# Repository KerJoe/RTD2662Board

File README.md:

# RTD2662Board

Prototype board for developing RTD2662 firmware.

## Known problems
1. CH341 can work either in I2C or UART mode, but not both at once. If R87 is present I2C mode is enabled, otherwise the UART is used. 
The "Mods/bridgeReplacementBoard" folder contains a patch PCB using MCP2221. While it is possible to use both I2C and UART parts simultaneously, I have experienced connection problems with it's USB interface.
2. The 3.3 volt rail lacks filtering enough capacitance, so it may be necessary to add an extra 100uF electrolytic capacitor across it and ground. The C78 capacitor was added to rectify the problem, but was not tested.
3. While TPS61040 can be used for driving an LED backlight, it requires a Zener diode between "BLO_ANO" line and ground, otherwise if the screen is disconnected it will output too much voltage and self destruct. A PT4103 or similar is recommended for the U5 backlight driver.

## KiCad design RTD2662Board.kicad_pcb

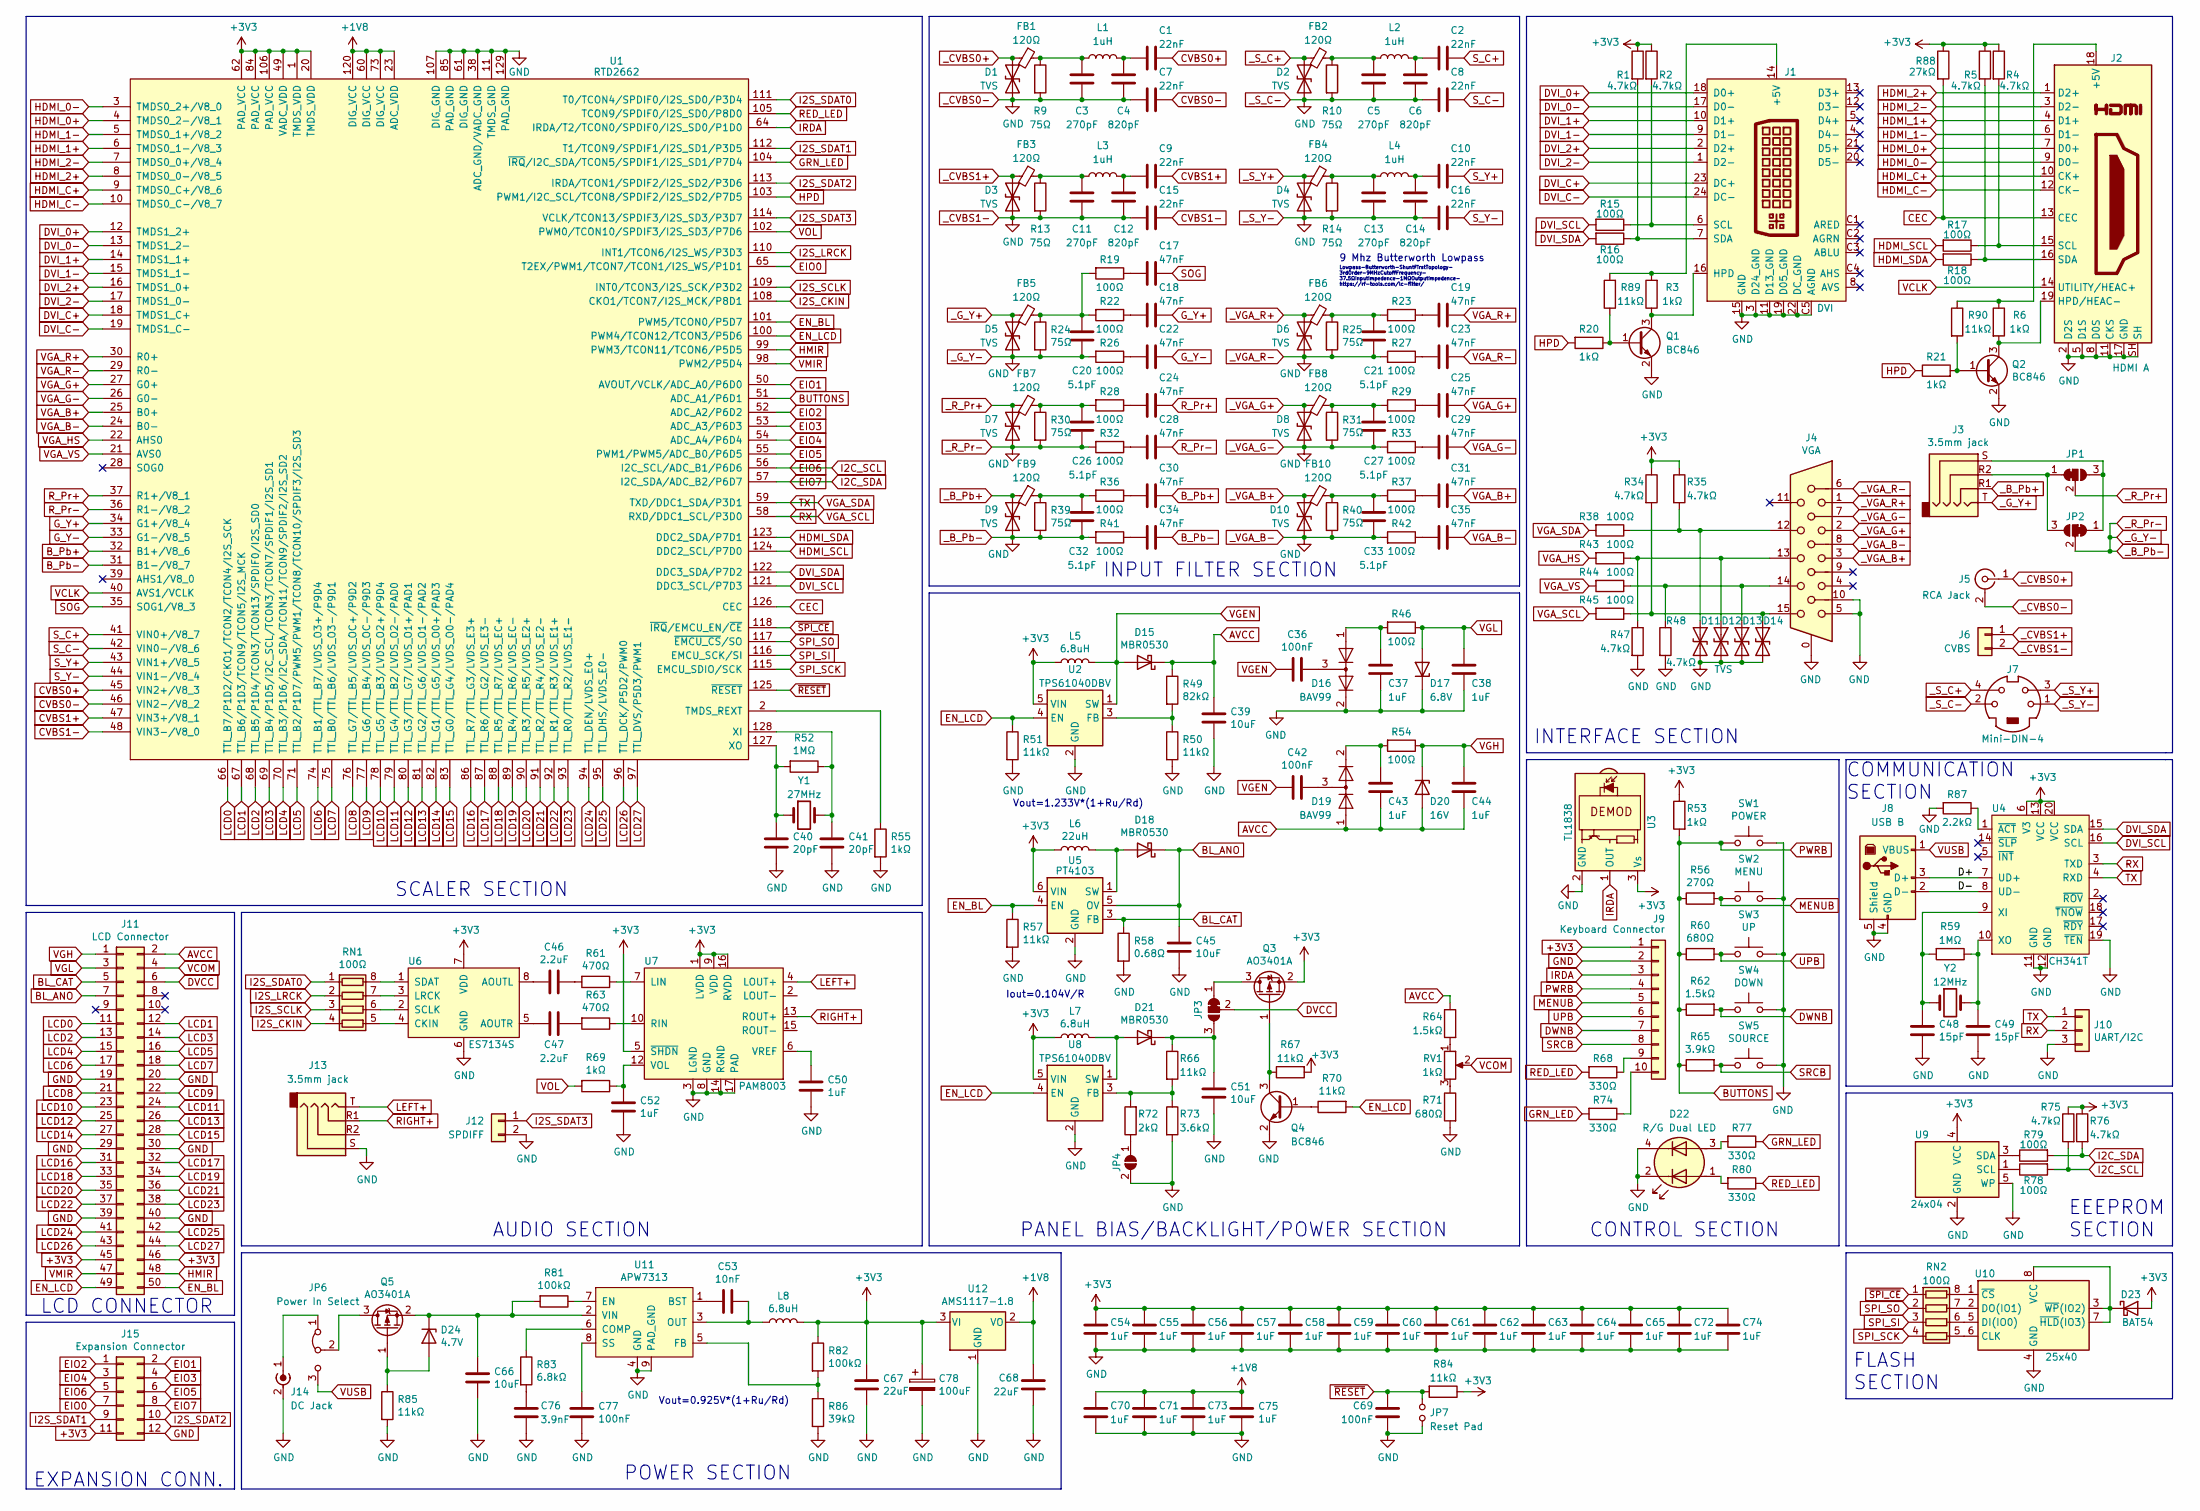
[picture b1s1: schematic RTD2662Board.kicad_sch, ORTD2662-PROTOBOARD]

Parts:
C1, C2, C7, C8, C9, C10, C15, C16: 22nF; C_0402_1005Metric_Pad0.74x0.62mm_HandSolder
C3, C5, C11, C13: 270pF; C_0402_1005Metric_Pad0.74x0.62mm_HandSolder
C4, C6, C12, C14: 820pF; C_0402_1005Metric_Pad0.74x0.62mm_HandSolder
C17, C18, C19, C22, C23, C24, C25, C28, C29, C30, C31, C34, C35: 47nF; C_0402_1005Metric_Pad0.74x0.62mm_HandSolder
C20, C21, C26, C27, C32, C33: 5.1pF; C_0402_1005Metric_Pad0.74x0.62mm_HandSolder
C36, C42, C69, C77: 100nF; C_0402_1005Metric_Pad0.74x0.62mm_HandSolder
C37, C38, C43, C44, C50, C52, C54, C55, C56, C57, C58, C59, C60, C61, C62, C63, C64, C65, C70, C71, C72, C73, C74, C75: 1uF; C_0402_1005Metric_Pad0.74x0.62mm_HandSolder
C39, C45, C51, C66: 10uF; C_0805_2012Metric_Pad1.18x1.45mm_HandSolder
C40, C41: 20pF; C_0402_1005Metric_Pad0.74x0.62mm_HandSolder
C46, C47: 2.2uF; C_0402_1005Metric_Pad0.74x0.62mm_HandSolder
C48, C49: 15pF; C_0402_1005Metric_Pad0.74x0.62mm_HandSolder
C53: 10nF; C_0402_1005Metric_Pad0.74x0.62mm_HandSolder
C67, C68: 22uF; C_0805_2012Metric_Pad1.18x1.45mm_HandSolder
C76: 3.9nF; C_0402_1005Metric_Pad0.74x0.62mm_HandSolder
C78: 100uF; CP_EIA-3528-21_Kemet-B
D1, D2, D3, D4, D5, D6, D7, D8, D9, D10, D11, D12, D13, D14: TVS; L_0402_1005Metric_Pad0.77x0.64mm_HandSolder
D15, D18, D21: MBR0530; D_SOD-123
D16, D19: BAV99; SOT-23
D17: 6.8V; D_SOD-323_HandSoldering
D20: 16V; D_SOD-323_HandSoldering
D22: R/G Dual LED; LED_Dual_0805_2012Metric
D23: BAT54; D_SOD-323_HandSoldering
D24: 4.7V; D_SOD-323_HandSoldering
FB1, FB2, FB3, FB4, FB5, FB6, FB7, FB8, FB9, FB10: 120Ω; L_0402_1005Metric_Pad0.77x0.64mm_HandSolder
J1: DVI
J2: HDMI A; HDMI_A
J3, J13: 3.5mm jack; Jack_3.5mm_PJ320D_Horizontal
J4: VGA; DSUB-15-HD_Female_Horizontal_P2.29x2.54mm
J5: RCA Jack; RCJ-013
J6: CVBS; PinHeader_1x02_P2.54mm_Vertical
J7: Mini-DIN-4; Mini-DIN_Female_6Pin_2rows
J8: USB B; USB_B_OST_USB-B1HSxx_Horizontal
J9: Keyboard Connector; JST_PH_B10B-PH-K_1x10_P2.00mm_Vertical
J10: UART/I2C; PinHeader_1x03_P2.54mm_Vertical
J11: LCD Connector; PinHeader_2x25_P1.27mm_Vertical_SMD_SmallPads
J12: SPDIFF; PinHeader_1x02_P2.54mm_Vertical
J14: DC Jack; BarrelJack_Horizontal
J15: Expansion Connector; PinHeader_2x06_P2.54mm_Vertical
JP1, JP2: Ring3/Sleeve GND Select; SolderJumper-3_P1.3mm_Bridged2Bar12_RoundedPad1.0x1.5mm
JP3: LCD Power Source Select; SolderJumper-3_P1.3mm_Bridged2Bar12_RoundedPad1.0x1.5mm
JP4: LCD Power Voltage Select; SolderJumper-2_P1.3mm_Open_RoundedPad1.0x1.5mm
JP6: Power In Select; PinSocket_1x03_P2.54mm_Vertical
JP7: Reset Pad; SolderJumper-2_P1.3mm_Open_Pad1.0x1.5mm
L1, L2, L3, L4: 1uH; L_0402_1005Metric_Pad0.77x0.64mm_HandSolder
L5, L7: 6.8uH; L_Bourns-SRN4018
L6: 22uH; L_Bourns-SRN4018
L8: 6.8uH; L_Bourns_SRN6045TA
Q1, Q2, Q4: BC846; SOT-23
Q3, Q5: AO3401A; SOT-23
R1, R2, R4, R5, R34, R35, R47, R48, R75, R76: 4.7kΩ; R_0402_1005Metric_Pad0.72x0.64mm_HandSolder
R3, R6, R20, R21, R53, R55, R69: 1kΩ; R_0402_1005Metric_Pad0.72x0.64mm_HandSolder
R9, R10, R13, R14, R24, R25, R30, R31, R39, R40: 75Ω; R_0402_1005Metric_Pad0.72x0.64mm_HandSolder
R15, R16, R17, R18, R19, R22, R23, R26, R27, R28, R29, R32, R33, R36, R37, R38, R41, R42, R43, R44, R45, R46, R54, R78, R79: 100Ω; R_0402_1005Metric_Pad0.72x0.64mm_HandSolder
R49: 82kΩ; R_0402_1005Metric_Pad0.72x0.64mm_HandSolder
R50, R51, R57, R66, R67, R70, R84, R85, R89, R90: 11kΩ; R_0402_1005Metric_Pad0.72x0.64mm_HandSolder
R52, R59: 1MΩ; R_0402_1005Metric_Pad0.72x0.64mm_HandSolder
R56: 270Ω; R_0402_1005Metric_Pad0.72x0.64mm_HandSolder
R58: 0.68Ω; R_1210_3225Metric_Pad1.30x2.65mm_HandSolder
R60, R71: 680Ω; R_0402_1005Metric_Pad0.72x0.64mm_HandSolder
R61, R63: 470Ω; R_0402_1005Metric_Pad0.72x0.64mm_HandSolder
R62, R64: 1.5kΩ; R_0402_1005Metric_Pad0.72x0.64mm_HandSolder
R65: 3.9kΩ; R_0402_1005Metric_Pad0.72x0.64mm_HandSolder
R68, R74, R77, R80: 330Ω; R_0402_1005Metric_Pad0.72x0.64mm_HandSolder
R72: 2kΩ; R_0402_1005Metric_Pad0.72x0.64mm_HandSolder
R73: 3.6kΩ; R_0402_1005Metric_Pad0.72x0.64mm_HandSolder
R81, R82: 100kΩ; R_0402_1005Metric_Pad0.72x0.64mm_HandSolder
R83: 6.8kΩ; R_0402_1005Metric_Pad0.72x0.64mm_HandSolder
R86: 39kΩ; R_0402_1005Metric_Pad0.72x0.64mm_HandSolder
R87: 2.2kΩ; R_0402_1005Metric_Pad0.72x0.64mm_HandSolder
R88: 27kΩ; R_0402_1005Metric_Pad0.72x0.64mm_HandSolder
RN1, RN2: 100Ω; R_Array_Convex_4x0603
RV1: 1kΩ; PVZ3A
SW1: POWER; SW_SPST_CK_RS282G05A3
SW2: MENU; SW_SPST_CK_RS282G05A3
SW3: UP; SW_SPST_CK_RS282G05A3
SW4: DOWN; SW_SPST_CK_RS282G05A3
SW5: SOURCE; SW_SPST_CK_RS282G05A3
U1: RTD2662; HLQFP-128-1EP_14x20mm_P0.5mm_EP7.11x8.26mm
U2, U8: TPS61040DBV; SOT-23-5
U3: TL1838; Vishay_MINICAST-3Pin
U4: CH341T; SSOP-20_5.3x7.2mm_P0.65mm_SmallPads
U5: PT4103; SOT-23-6
U6: ES7134S; SOIC-8_3.9x4.9mm_P1.27mm
U7: PAM8003; HSOP-16-1EP_3.9x9.9mm_P1.27mm_EP2.41x4.1mm
U9: 24x04; SOT-23-5
U10: 25x40; SOIC-8_3.9x4.9mm_P1.27mm_DIP-8_W7.62mm_Socket
U11: APW7313; HSOP-8-1EP_3.9x4.9mm_P1.27mm_EP2.41x3.1mm
U12: AMS1117-1.8; SOT-223-3_TabPin2
Y1: 27MHz; Crystal_SMD_HC49-SD+HC49-U
Y2: 12MHz; Crystal_SMD_HC49-SD+HC49-U

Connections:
+1V8: C68.1, C70.1, C71.1, C73.1, C75.1, U1.23 (ADC_VDD), U1.60 (DIG_VCC), U1.73 (DIG_VCC), U1.120 (DIG_VCC), U12.2 (VO)
+3V3: C54.1, C55.1, C56.1, C57.1, C58.1, C59.1, C60.1, C61.1, C62.1, C63.1, C64.1, C65.1, C67.1, C72.1, C74.1, C78.1, D23.2 (A), J9.1, J11.45, J11.46, J15.11, L5.1, L6.1, L7.1, L8.2, Q3.2 (S), R1.1, R2.1, R4.1, R5.1, R34.1, R35.1, R53.1, R67.2, R75.1, R76.1, R82.1, R84.1, R88.1, U1.1 (TMDS_VDD), U1.20 (TMDS_VDD), U1.49 (VADC_VDD), U1.62 (PAD_VCC), U1.84 (PAD_VCC), U1.106 (PAD_VCC), U2.5 (VIN), U3.3 (Vs), U4.6 (V3), U4.13 (VCC), U4.20 (VCC), U5.6 (VIN), U6.7 (VDD), U7.1 (LVDD), U7.5 (~SHDN), U7.9 (VDD), U7.16 (RVDD), U8.5 (VIN), U9.4 (VCC), U12.3 (VI)
/D+: J8.3 (D+), U4.7 (UD+)
/D-: J8.2 (D-), U4.8 (UD-)
AVCC: C39.1, C43.1, C44.1, D15.1 (K), D19.1 (K), D20.2 (A), J11.2, R49.1, R64.1
BL_ANO: C45.1, D18.1 (K), J11.7, U5.5 (OV)
BL_CAT: J11.5, R58.1, U5.3 (FB)
BUTTONS: J9.4, R53.2, R56.1, R60.1, R62.1, R65.1, SW1.2, U1.51 (ADC_A1/P6D1)
B_Pb+: C30.1, U1.32 (B1+/V8_6)
B_Pb-: C34.1, U1.31 (B1-/V8_7)
CEC: J2.13 (CEC), R88.2, U1.126 (CEC)
CVBS0+: C1.1, U1.45 (VIN2+/V8_3)
CVBS0-: C7.1, U1.46 (VIN2-/V8_2)
CVBS1+: C9.1, U1.47 (VIN3+/V8_1)
CVBS1-: C15.1, U1.48 (VIN3-/V8_0)
DVCC: J11.6, JP3.2 (C)
DVI_0+: J1.18 (D0+), U1.12 (TMDS1_2+)
DVI_0-: J1.17 (D0-), U1.13 (TMDS1_2-)
DVI_1+: J1.10 (D1+), U1.14 (TMDS1_1+)
DVI_1-: J1.9 (D1-), U1.15 (TMDS1_1-)
DVI_2+: J1.2 (D2+), U1.16 (TMDS1_0+)
DVI_2-: J1.1 (D2-), U1.17 (TMDS1_0-)
DVI_C+: J1.23 (DC+), U1.18 (TMDS1_C+)
DVI_C-: J1.24 (DC-), U1.19 (TMDS1_C-)
DVI_SCL: R15.2, U1.121 (DDC3_SCL/P7D3), U4.16 (SCL)
DVI_SDA: R16.2, U1.122 (DDC3_SDA/P7D2), U4.15 (SDA)
DWNB: J9.7, R62.2, SW4.2
EIO0: J15.7, U1.65 (T2EX/PWM1/TCON7/TCON1/I2S_WS/P1D1)
EIO1: J15.2, U1.50 (AVOUT/VCLK/ADC_A0/P6D0)
EIO2: J15.1, U1.52 (ADC_A2/P6D2)
EIO3: J15.4, U1.53 (ADC_A3/P6D3)
EIO4: J15.3, U1.54 (ADC_A4/P6D4)
EIO5: J15.6, U1.55 (PWM1/PWM5/ADC_B0/P6D5)
EIO6: J15.5, R75.2, R79.2, U1.56 (I2C_SCL/ADC_B1/P6D6)
EIO7: J15.8, R76.2, R78.2, U1.57 (I2C_SDA/ADC_B2/P6D7)
EN_BL: J11.50, R57.1, U1.101 (PWM5/TCON0/P5D7), U5.4 (EN)
EN_LCD: J11.49, R51.1, R70.2, U1.100 (PWM4/TCON12/TCON3/P5D6), U2.4 (EN), U8.4 (EN)
GND: C3.2, C4.2, C5.2, C6.2, C7.2, C8.2, C11.2, C12.2, C13.2, C14.2, C15.2, C16.2, C20.2, C21.1, C26.2, C27.1, C32.2, C33.1, C37.1, C38.1, C39.2, C40.2, C41.2, C45.2, C48.2, C49.2, C50.2, C51.2, C52.2, C54.2, C55.2, C56.2, C57.2, C58.2, C59.2, C60.2, C61.2, C62.2, C63.2, C64.2, C65.2, C66.2, C67.2, C68.2, C69.2, C70.2, C71.2, C72.2, C73.2, C74.2, C75.2, C76.2, C77.2, C78.2, D1.2 (A2), D2.2 (A2), D3.2 (A2), D4.2 (A2), D5.2 (A2), D6.2 (A2), D7.2 (A2), D8.2 (A2), D9.2 (A2), D10.2 (A2), D11.2 (A2), D12.2 (A2), D13.2 (A2), D14.2 (A2), D16.2 (A), D17.1 (K), D22.2 (K1), D22.4 (K2), J1.3 (D24_GND), J1.11 (D13_GND), J1.15 (GND), J1.19 (D05_GND), J1.22 (DC_GND), J1.C5 (AGND), J2.2 (D2S), J2.5 (D1S), J2.8 (D0S), J2.11 (CKS), J2.17 (GND), J2.SH, J4.0, J4.5, J4.6, J4.7, J4.8, J4.10, J5.2 (Ext), J6.2, J7.1, J7.2, J8.4 (GND), J8.5 (Shield), J9.2, J10.3, J11.19, J11.20, J11.29, J11.30, J11.39, J11.40, J12.2, J13.S, J14.2 (Ext), J15.12, JP2.2 (C), JP4.2 (B), JP7.2, Q1.2 (E), Q2.2 (E), Q4.2 (E), R9.2, R10.2, R13.2, R14.2, R24.2, R25.2, R26.2, R27.2, R30.2, R31.2, R32.2, R33.2, R39.2, R40.2, R41.2, R42.2, R47.2, R48.2, R50.2, R51.2, R55.2, R57.2, R58.2, R71.2, R73.2, R85.2, R86.2, R87.2, SW1.1, SW2.1, SW3.1, SW4.1, SW5.1, U1.11 (TMDS_GND), U1.38 (ADC_GND/VADC_GND), U1.61 (DIG_GND), U1.85 (PAD_GND), U1.107 (DIG_GND), U1.129 (PAD_GND), U2.2 (GND), U3.2 (GND), U4.11 (GND), U4.12 (GND), U4.19 (~TEN), U5.2 (GND), U6.6 (GND), U7.3 (LGND), U7.8 (GND), U7.14 (RGND), U7.17 (PAD), U8.2 (GND), U9.2 (GND), U9.5 (WP), U10.4 (GND), U11.4 (GND), U11.9 (PAD_GND), U12.1 (GND)
GRN_LED: R74.2, R77.1, U1.104 (~IRQ/I2C_SDA/TCON5/SPDIF1/I2S_SD1/P7D4)
G_Y+: C18.1, U1.34 (G1+/V8_4)
G_Y-: C22.1, U1.33 (G1-/V8_5)
HDMI_0+: J2.7 (D0+), U1.4 (TMDS0_2-/V8_1)
HDMI_0-: J2.9 (D0-), U1.3 (TMDS0_2+/V8_0)
HDMI_1+: J2.4 (D1+), U1.6 (TMDS0_1-/V8_3)
HDMI_1-: J2.6 (D1-), U1.5 (TMDS0_1+/V8_2)
HDMI_2+: J2.1 (D2+), U1.8 (TMDS0_0-/V8_5)
HDMI_2-: J2.3 (D2-), U1.7 (TMDS0_0+/V8_4)
HDMI_C+: J2.10 (CK+), U1.9 (TMDS0_C+/V8_6)
HDMI_C-: J2.12 (CK-), U1.10 (TMDS0_C-/V8_7)
HDMI_SCL: R17.2, U1.124 (DDC2_SCL/P7D0)
HDMI_SDA: R18.2, U1.123 (DDC2_SDA/P7D1)
HMIR: J11.48, U1.99 (PWM3/TCON11/TCON6/P5D5)
HPD: R20.2, R21.1, U1.103 (PWM1/I2C_SCL/TCON8/SPDIF2/I2S_SD2/P7D5)
I2S_CKIN: RN1.4 (R4.1), U1.108 (CKO1/TCON7/I2S_MCK/P8D1)
I2S_LRCK: RN1.2 (R2.1), U1.110 (INT1/TCON6/I2S_WS/P3D3)
I2S_SCLK: RN1.3 (R3.1), U1.109 (INT0/TCON3/I2S_SCK/P3D2)
I2S_SDAT0: RN1.1 (R1.1), U1.111 (T0/TCON4/SPDIF0/I2S_SD0/P3D4)
I2S_SDAT1: J15.9, U1.112 (T1/TCON9/SPDIF1/I2S_SD1/P3D5)
I2S_SDAT2: J15.10, U1.113 (IRDA/TCON1/SPDIF2/I2S_SD2/P3D6)
I2S_SDAT3: J12.1, U1.114 (VCLK/TCON13/SPDIF3/I2S_SD3/P3D7)
IRDA: J9.3, U1.64 (IRDA/T2/TCON0/SPDIF0/I2S_SD0/P1D0), U3.1 (OUT)
LCD0: J11.11, U1.66 (TTL_B7/P1D2/CKO1/TCON2/TCON4/I2S_SCK)
LCD1: J11.12, U1.67 (TTL_B6/P1D3/TCON9/TCON5/I2S_MCK)
LCD2: J11.13, U1.68 (TTL_B5/P1D4/TCON3/TCON13/SPDIF0/I2S_SD0)
LCD3: J11.14, U1.69 (TTL_B4/P1D5/I2C_SCL/TCON3/TCON7/SPDIF1/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)
LCD4: J11.15, U1.70 (TTL_B3/P1D6/I2C_SDA/TCON11/TCON9/SPDIF2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)
LCD5: J11.16, U1.71 (TTL_B2/P1D7/PWM5/PWM1/TCON8/TCON10/SPDI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)
LCD6: J11.17, U1.74 (TTL_B1/TTL_B7/LVDS_O3+/P9D4)
LCD7: J11.18, U1.75 (TTL_B0/TTL_B6/LVDS_O3-/P9D1)
LCD8: J11.21, U1.76 (TTL_G7/TTL_B5/LVDS_OC+/P9D2)
LCD9: J11.22, U1.77 (TTL_G6/TTL_B4/LVDS_OC-/P9D3)
LCD10: J11.23, U1.78 (TTL_G5/TTL_B3/LVDS_O2+/P9D4)
LCD11: J11.24, U1.79 (TTL_G4/TTL_B2/LVDS_O2-/PAD0)
LCD12: J11.25, U1.80 (TTL_G3/TTL_G7/LVDS_O1+/PAD1)
LCD13: J11.26, U1.81 (TTL_G2/TTL_G6/LVDS_O1-/PAD2)
LCD14: J11.27, U1.82 (TTL_G1/TTL_G5/LVDS_O0+/PAD3)
LCD15: J11.28, U1.83 (TTL_G0/TTL_G4/LVDS_O0-/PAD4)
LCD16: J11.31, U1.86 (TTL_R7/TTL_G3/LVDS_E3+)
LCD17: J11.32, U1.87 (TTL_R6/TTL_G2/LVDS_E3-)
LCD18: J11.33, U1.88 (TTL_R5/TTL_R7/LVDS_EC+)
LCD19: J11.34, U1.89 (TTL_R4/TTL_R6/LVDS_EC-)
LCD20: J11.35, U1.90 (TTL_R3/TTL_R5/LVDS_E2+)
LCD21: J11.36, U1.91 (TTL_R2/TTL_R4/LVDS_E2-)
LCD22: J11.37, U1.92 (TTL_R1/TTL_R3/LVDS_E1+)
LCD23: J11.38, U1.93 (TTL_R0/TTL_R2/LVDS_E1-)
LCD24: J11.41, U1.94 (TTL_DEN/LVDS_E0+)
LCD25: J11.42, U1.95 (TTL_DHS/LVDS_E0-)
LCD26: J11.43, U1.96 (TTL_DCK/P5D2/PWM0)
LCD27: J11.44, U1.97 (TTL_DVS/P5D3/PWM1)
LEFT+: J13.T, U7.4 (LOUT+)
MENUB: J9.5, R56.2, SW2.2
unnamed: C1.2, C4.1, L1.2
unnamed: C2.2, C6.1, L2.2
unnamed: C3.1, FB1.1, L1.1, R9.1
unnamed: C5.1, FB2.1, L2.1, R10.1
unnamed: C10.2, C14.1, L4.2
unnamed: C11.1, FB3.1, L3.1, R13.1
unnamed: C9.2, C12.1, L3.2
unnamed: C13.1, FB4.1, L4.1, R14.1
unnamed: C17.2, R19.1
unnamed: C18.2, R22.1
unnamed: C19.2, R23.1
unnamed: C20.1, FB5.1, R19.2, R22.2, R24.1
unnamed: C21.2, FB6.1, R23.2, R25.1
unnamed: C22.2, R26.1
unnamed: C23.2, R27.1
unnamed: C24.2, R28.1
unnamed: C25.2, R29.1
unnamed: C26.1, FB7.1, R28.2, R30.1
unnamed: C27.2, FB8.1, R29.2, R31.1
unnamed: C28.2, R32.1
unnamed: C29.2, R33.1
unnamed: C30.2, R36.1
unnamed: C31.2, R37.1
unnamed: C32.1, FB9.1, R36.2, R39.1
unnamed: C33.2, FB10.1, R37.2, R40.1
unnamed: C34.2, R41.1
unnamed: C35.2, R42.1
unnamed: C36.1, D16.3 (K)
unnamed: C37.2, D16.1 (K), R46.2
unnamed: C42.1, D19.3 (K)
unnamed: C46.1, R61.2
unnamed: C47.1, R63.2
unnamed: C76.1, R83.2
unnamed: D11.1 (A1), J4.12, R35.2, R38.1
unnamed: D12.1 (A1), J4.13, R43.1, R47.1
unnamed: D13.1 (A1), J4.14, R44.1, R48.1
unnamed: D14.1 (A1), J4.15, R34.2, R45.1
unnamed: D18.2 (A), L6.2, U5.1 (SW)
unnamed: C43.2, D19.2 (A), R54.2
unnamed: D21.2 (A), L7.2, U8.1 (SW)
unnamed: C51.1, D21.1 (K), JP3.3 (B), R66.1
unnamed: D22.1 (A1), R80.2
unnamed: D22.3 (A2), R77.2
unnamed: D23.1 (K), U10.3 (~WP(IO2)), U10.7 (~HLD(IO3)), U10.8 (VCC)
unnamed: D24.2 (A), Q5.1 (G), R85.1
unnamed: C66.1, D24.1 (K), Q5.2 (S), R81.2, U11.2 (VIN)
unnamed: J1.14 (+5V), R3.2, R89.2
unnamed: J1.16 (HPD), Q1.3 (C), R3.1
unnamed: J1.6 (SCL), R2.2, R15.1
unnamed: J1.7 (SDA), R1.2, R16.1
unnamed: J2.18 (+5V), R6.1, R90.1
unnamed: J2.19 (HPD/HEAC-), Q2.3 (C), R6.2
unnamed: J2.15 (SCL), R5.2, R17.1
unnamed: J2.16 (SDA), R4.2, R18.1
unnamed: J9.9, R68.1
unnamed: J9.10, R74.1
unnamed: J14.1 (In), JP6.1 (A)
unnamed: J3.R2, JP1.1 (A), JP2.3 (B)
unnamed: J3.S, JP1.3 (B), JP2.1 (A)
unnamed: JP3.1 (A), Q3.3 (D)
unnamed: JP4.1 (A), R72.1
unnamed: JP6.2 (C), Q5.3 (D)
unnamed: Q1.1 (B), R20.1, R89.1
unnamed: Q2.1 (B), R21.2, R90.2
unnamed: Q3.1 (G), Q4.3 (C), R67.1
unnamed: Q4.1 (B), R70.1
unnamed: R64.2, RV1.1
unnamed: R71.1, RV1.3
unnamed: RN1.8 (R1.2), U6.1 (SDAT)
unnamed: RN1.7 (R2.2), U6.3 (LRCK)
unnamed: RN1.6 (R3.2), U6.2 (SCLK)
unnamed: RN1.5 (R4.2), U6.4 (CKIN)
unnamed: RN2.8 (R1.2), U10.1 (~CS)
unnamed: RN2.7 (R2.2), U10.2 (DO(IO1))
unnamed: RN2.6 (R3.2), U10.5 (DI(IO0))
unnamed: RN2.5 (R4.2), U10.6 (CLK)
unnamed: R55.1, U1.2 (TMDS_REXT)
unnamed: C41.1, R52.1, U1.128 (XI), Y1.2
unnamed: C40.1, R52.2, U1.127 (XO), Y1.1
unnamed: R49.2, R50.1, U2.3 (FB)
unnamed: C48.1, R59.2, U4.9 (XI), Y2.1
unnamed: C49.1, R59.1, U4.10 (XO), Y2.2
unnamed: R87.1, U4.1 (~ACT)
unnamed: C46.2, U6.8 (AOUTL)
unnamed: C47.2, U6.5 (AOUTR)
unnamed: R61.1, U7.7 (LIN)
unnamed: R63.1, U7.10 (RIN)
unnamed: C52.1, R69.1, U7.12 (VOL)
unnamed: C50.1, U7.6 (VREF)
unnamed: R66.2, R72.2, R73.1, U8.3 (FB)
unnamed: R79.1, U9.1 (SCL)
unnamed: R78.1, U9.3 (SDA)
unnamed: C53.1, U11.1 (BST)
unnamed: R83.1, U11.6 (COMP)
unnamed: R81.1, U11.7 (EN)
unnamed: R82.2, R86.1, U11.5 (FB)
unnamed: C53.2, L8.1, U11.3 (OUT)
unnamed: C77.1, U11.8 (SS)
RED_LED: R68.2, R80.1, U1.105 (TCON9/SPDIF0/I2S_SD0/P8D0)
RIGHT+: J13.R1, U7.13 (ROUT+)
RX: J10.2, R45.2, U1.58 (RXD/DDC1_SCL/P3D0), U4.3 (TXD)
R_Pr+: C24.1, U1.37 (R1+/V8_1)
R_Pr-: C28.1, U1.36 (R1-/V8_2)
SOG: C17.1, U1.35 (SOG1/V8_3)
SPI_SCK: RN2.4 (R4.1), U1.115 (EMCU_SDIO/SCK)
SPI_SI: RN2.3 (R3.1), U1.116 (EMCU_SCK/SI)
SPI_SO: RN2.2 (R2.1), U1.117 (~EMCU_CS/SO)
SRCB: J9.8, R65.2, SW5.2
S_C+: C2.1, U1.41 (VIN0+/V8_7)
S_C-: C8.1, U1.42 (VIN0-/V8_6)
S_Y+: C10.1, U1.43 (VIN1+/V8_5)
S_Y-: C16.1, U1.44 (VIN1-/V8_4)
TX: J10.1, R38.2, U1.59 (TXD/DDC1_SDA/P3D1), U4.4 (RXD)
UPB: J9.6, R60.2, SW3.2
VCLK: J2.14 (UTILITY/HEAC+), U1.40 (AVS1/VCLK)
VCOM: J11.4, RV1.2
VGA_B+: C31.1, U1.25 (B0+)
VGA_B-: C35.1, U1.24 (B0-)
VGA_G+: C25.1, U1.27 (G0+)
VGA_G-: C29.1, U1.26 (G0-)
VGA_HS: R43.2, U1.22 (AHS0)
VGA_R+: C19.1, U1.30 (R0+)
VGA_R-: C23.1, U1.29 (R0-)
VGA_VS: R44.2, U1.21 (AVS0)
VGEN: C36.2, C42.2, D15.2 (A), L5.2, U2.1 (SW)
VGH: C44.2, D20.1 (K), J11.1, R54.1
VGL: C38.2, D17.2 (A), J11.3, R46.1
VMIR: J11.47, U1.98 (PWM2/P5D4)
VOL: R69.2, U1.102 (PWM0/TCON10/SPDIF3/I2S_SD3/P7D6)
VUSB: J8.1 (VBUS), JP6.3 (B)
_B_Pb+: D9.1 (A1), FB9.2, J3.R1
_CVBS0+: D1.1 (A1), FB1.2, J5.1 (In)
_CVBS1+: D3.1 (A1), FB3.2, J6.1
_G_Y+: D5.1 (A1), FB5.2, J3.T
_R_Pr+: D7.1 (A1), FB7.2, JP1.2 (C)
_S_C+: D2.1 (A1), FB2.2, J7.4
_S_Y+: D4.1 (A1), FB4.2, J7.3
_VGA_B+: D10.1 (A1), FB10.2, J4.3
_VGA_G+: D8.1 (A1), FB8.2, J4.2
_VGA_R+: D6.1 (A1), FB6.2, J4.1
~RESET: C69.1, JP7.1, R84.2, U1.125 (~RESET)
~SPI_CE: RN2.1 (R1.1), U1.118 (~IRQ/EMCU_EN/~CE)

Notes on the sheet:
COMMUNICATION SECTION
Vout=0.925V*(1+Ru/Rd)
Iout=0.104V/R
CONTROL SECTION
INTERFACE SECTION
Vout=1.233V*(1+Ru/Rd)
Lowpass-Butterworth-ShuntFirstTopology- 3rdOrder-9MHzCutoffFrequency- 37.5ΩInputImpedence-1MΩOutputImpedence- https://rf-tools.com/lc-filter/
POWER SECTION
9 Mhz Butterworth Lowpass
EXPANSION CONN.
SCALER SECTION
LCD CONNECTOR
AUDIO SECTION
EEEPROM SECTION
INPUT FILTER SECTION
FLASH SECTION
PANEL BIAS/BACKLIGHT/POWER SECTION

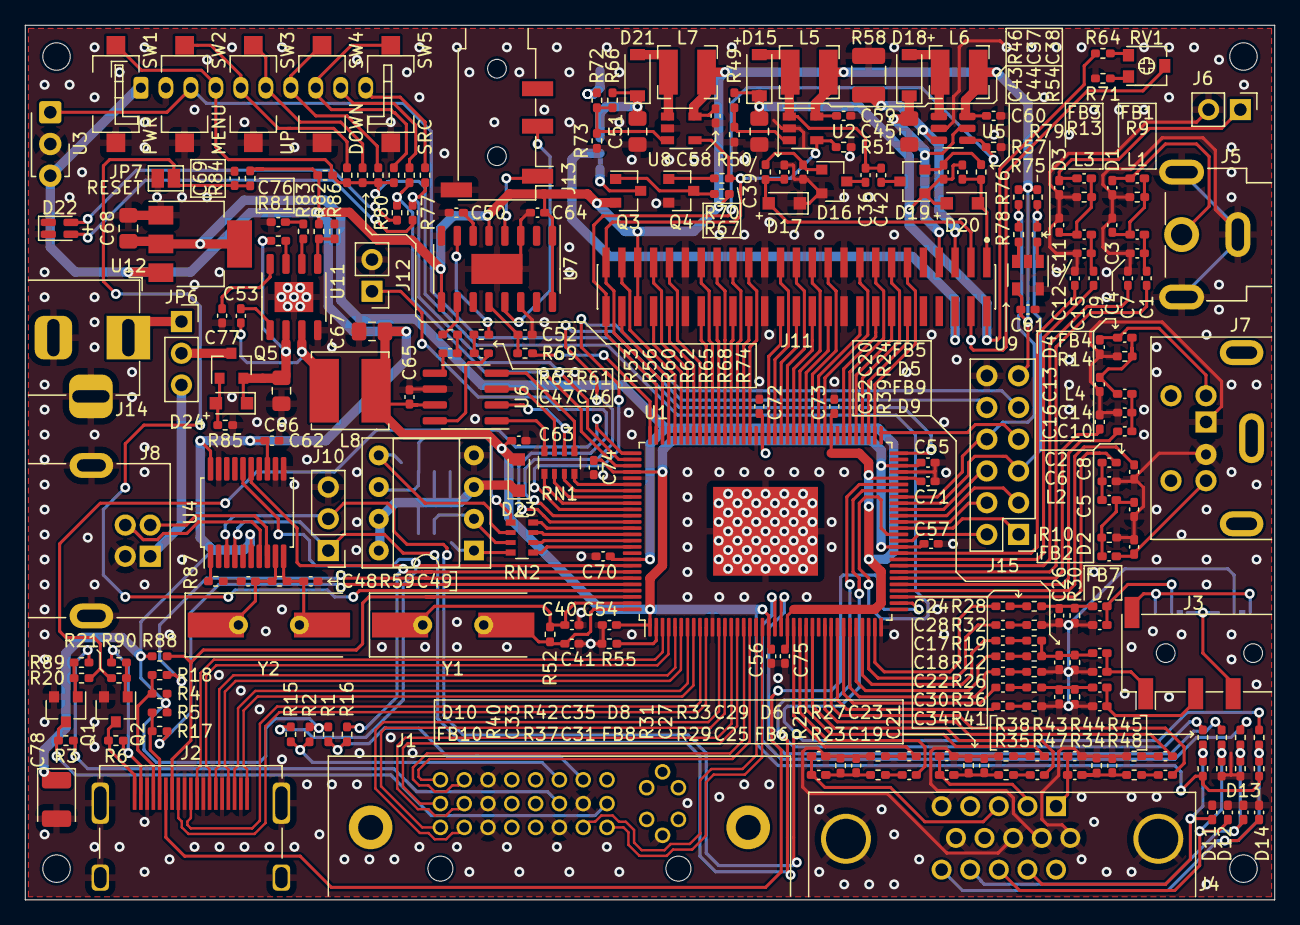
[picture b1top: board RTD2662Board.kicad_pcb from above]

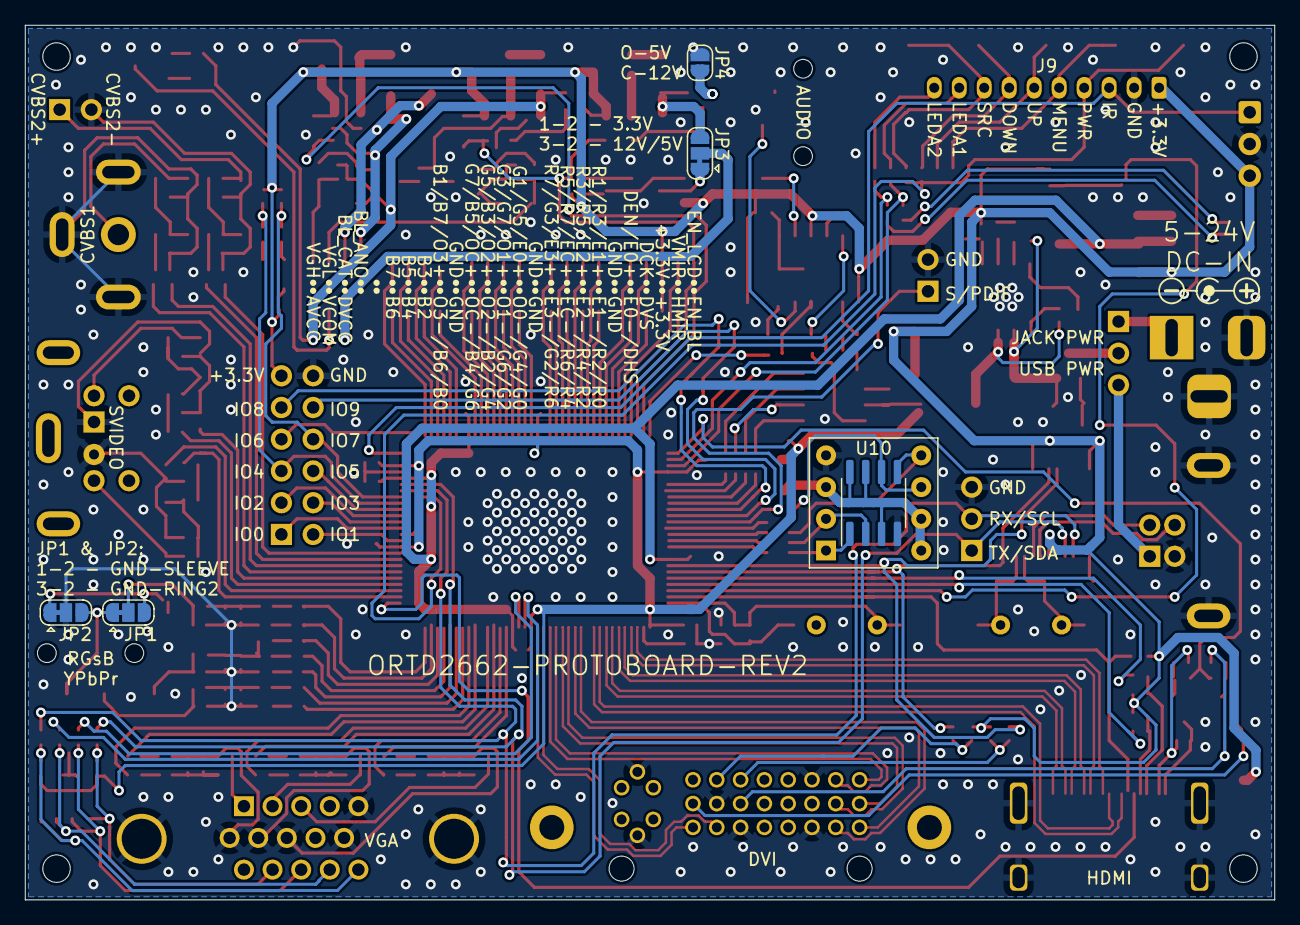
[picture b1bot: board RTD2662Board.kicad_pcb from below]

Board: 2 copper layers, 100.0 x 70.0 mm, 254 parts (4 on the bottom side), 233 nets.

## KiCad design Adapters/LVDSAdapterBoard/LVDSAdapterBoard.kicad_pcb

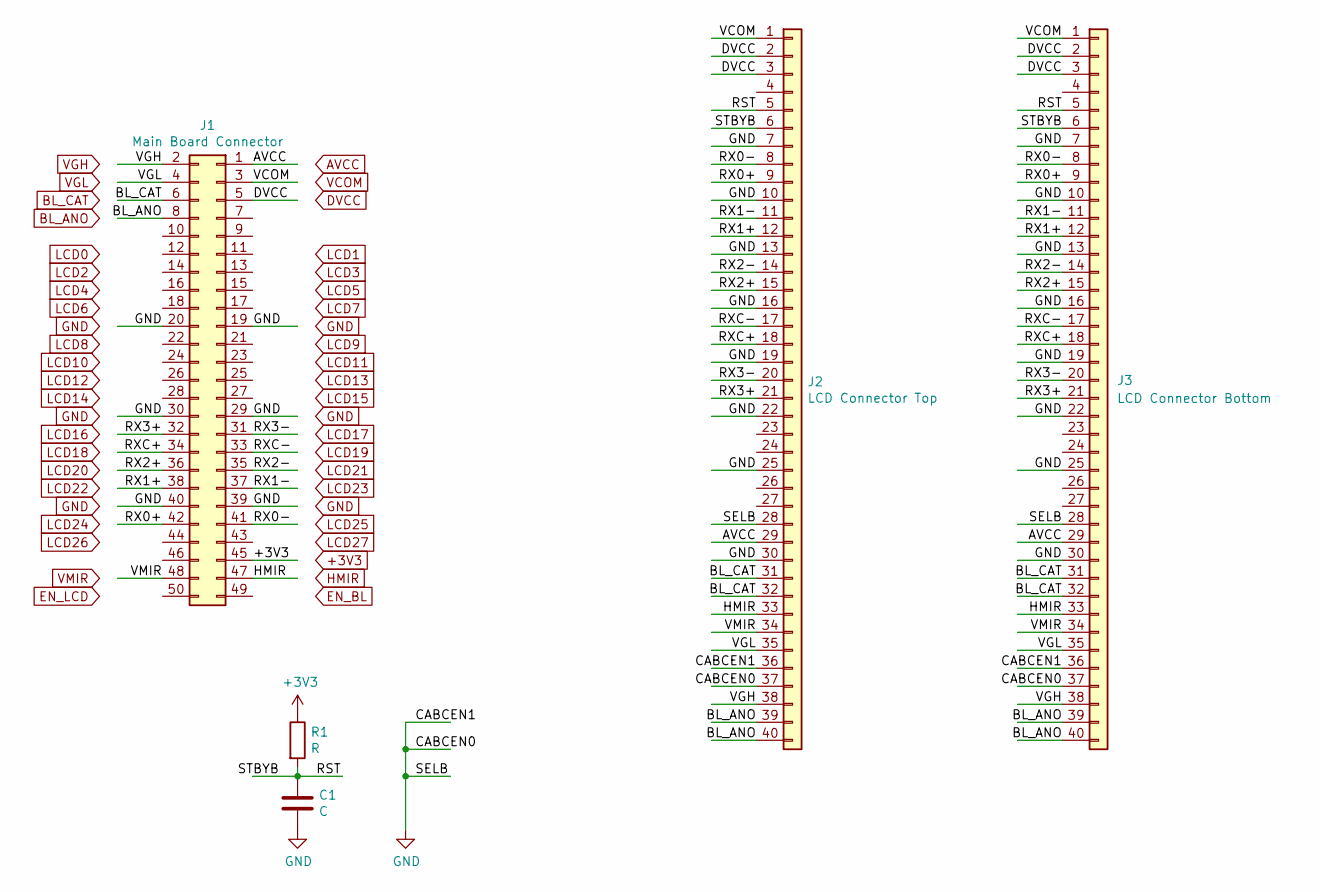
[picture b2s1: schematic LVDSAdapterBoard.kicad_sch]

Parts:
C1: C; C_0402_1005Metric_Pad0.74x0.62mm_HandSolder
J1: Main Board Connector; PinHeader_2x25_P1.27mm_Vertical_SMD_SmallPads
J2: LCD Connector Top; GenericConnFFC_1x40_P0.5mm_Horizontal_Reversed
J3: LCD Connector Bottom; GenericConnFFC_1x40_P0.5mm_Horizontal
R1: R; R_0402_1005Metric_Pad0.72x0.64mm_HandSolder

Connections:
+3V3: J1.45, R1.1
/RST: C1.1, J2.5, J2.6, J3.5, J3.6, R1.2
/RX0+: J1.42, J2.9, J3.9
/RX0-: J1.41, J2.8, J3.8
/RX1+: J1.38, J2.12, J3.12
/RX1-: J1.37, J2.11, J3.11
/RX2+: J1.36, J2.15, J3.15
/RX2-: J1.35, J2.14, J3.14
/RX3+: J1.32, J2.21, J3.21
/RX3-: J1.31, J2.20, J3.20
/RXC+: J1.34, J2.18, J3.18
/RXC-: J1.33, J2.17, J3.17
AVCC: J1.1, J2.29, J3.29
BL_ANO: J1.8, J2.39, J2.40, J3.39, J3.40
BL_CAT: J1.6, J2.31, J2.32, J3.31, J3.32
DVCC: J1.5, J2.2, J2.3, J3.2, J3.3
GND: C1.2, J1.19, J1.20, J1.29, J1.30, J1.39, J1.40, J2.7, J2.10, J2.13, J2.16, J2.19, J2.22, J2.25, J2.28, J2.30, J2.36, J2.37, J3.7, J3.10, J3.13, J3.16, J3.19, J3.22, J3.25, J3.28, J3.30, J3.36, J3.37
HMIR: J1.47, J2.33, J3.33
VCOM: J1.3, J2.1, J3.1
VGH: J1.2, J2.38, J3.38
VGL: J1.4, J2.35, J3.35
VMIR: J1.48, J2.34, J3.34

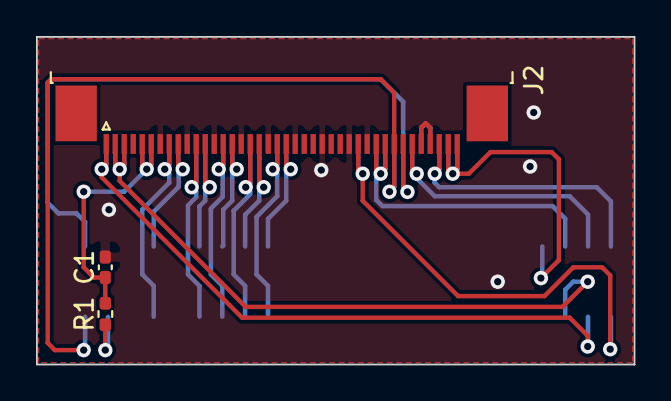
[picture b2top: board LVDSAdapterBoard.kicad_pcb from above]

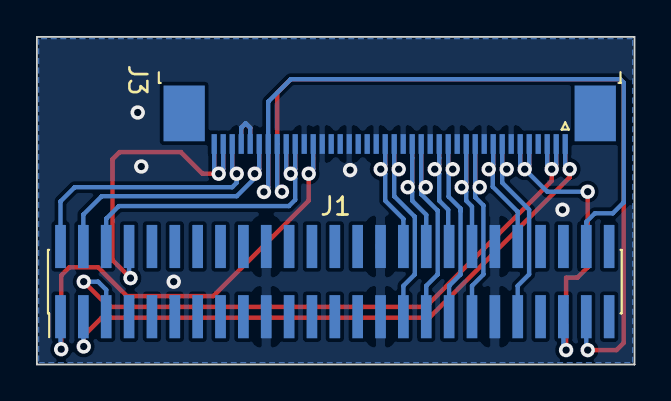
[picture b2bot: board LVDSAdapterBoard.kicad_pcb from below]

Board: 2 copper layers, 33.2 x 18.2 mm, 5 parts (2 on the bottom side), 22 nets.

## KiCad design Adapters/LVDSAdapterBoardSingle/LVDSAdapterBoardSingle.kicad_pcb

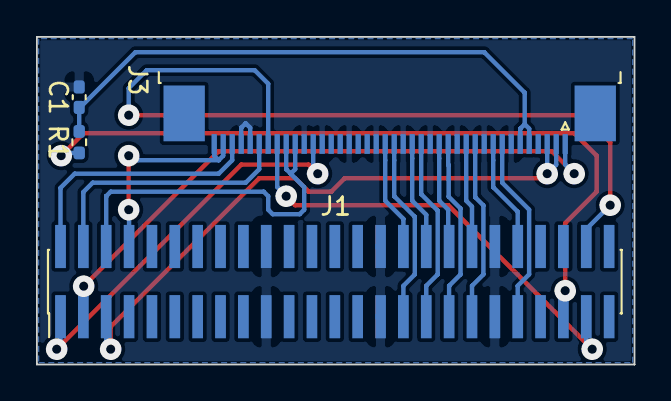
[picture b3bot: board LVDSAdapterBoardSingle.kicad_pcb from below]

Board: 2 copper layers, 33.2 x 18.2 mm, 4 parts (4 on the bottom side), 22 nets.

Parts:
C1: C; C_0402_1005Metric_Pad0.74x0.62mm_HandSolder
J1: Main Board Connector; PinHeader_2x25_P1.27mm_Vertical_SMD_SmallPads
J3: LCD Connector Bottom; GenericConnFFC_1x40_P0.5mm_Horizontal
R1: R; R_0402_1005Metric_Pad0.72x0.64mm_HandSolder

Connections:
+3V3: J1.45, R1.1
/RST: C1.1, J3.5, J3.6, R1.2
/RX0+: J1.42, J3.9
/RX0-: J1.41, J3.8
/RX1+: J1.38, J3.12
/RX1-: J1.37, J3.11
/RX2+: J1.36, J3.15
/RX2-: J1.35, J3.14
/RX3+: J1.32, J3.21
/RX3-: J1.31, J3.20
/RXC+: J1.34, J3.18
/RXC-: J1.33, J3.17
AVCC: J1.1, J3.29
BL_ANO: J1.8, J3.39, J3.40
BL_CAT: J1.6, J3.31, J3.32
DVCC: J1.5, J3.2, J3.3
GND: C1.2, J1.19, J1.20, J1.29, J1.30, J1.39, J1.40, J3.7, J3.10, J3.13, J3.16, J3.19, J3.22, J3.25, J3.28, J3.30, J3.36, J3.37
HMIR: J1.47, J3.33
VCOM: J1.3, J3.1
VGH: J1.2, J3.38
VGL: J1.4, J3.35
VMIR: J1.48, J3.34

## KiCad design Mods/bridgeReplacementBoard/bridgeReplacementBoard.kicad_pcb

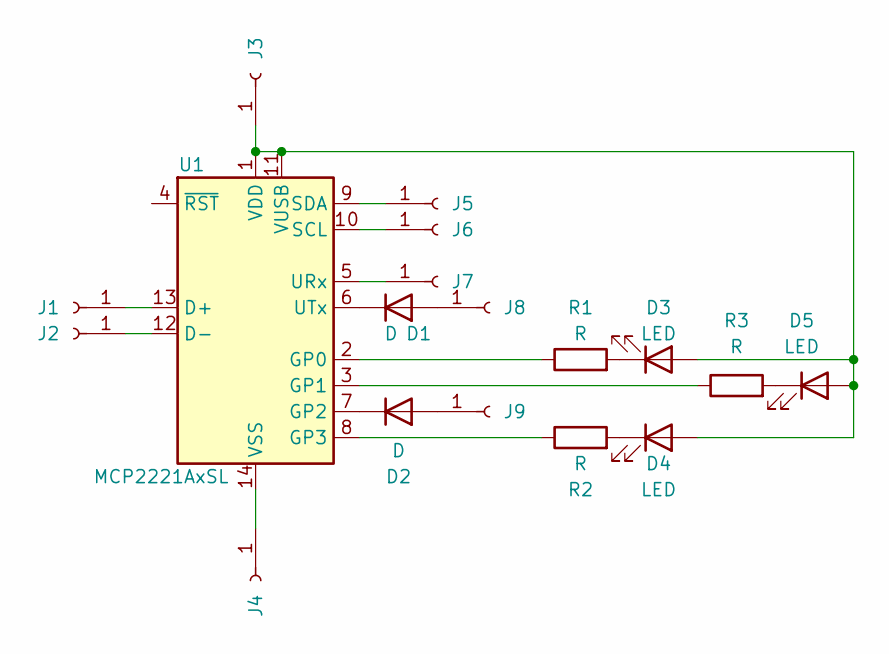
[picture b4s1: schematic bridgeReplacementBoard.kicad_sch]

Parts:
D1, D2: D; D_SOD-323_HandSoldering
D3, D4, D5: LED; LED_0603_1608Metric_Pad1.05x0.95mm_HandSolder
J1, J2, J3, J4, J5, J6, J7, J8, J9: Conn_01x01_Female; SolderWirePad_1x01_SMD_1x2mm
R1, R2, R3: R; R_0402_1005Metric_Pad0.72x0.64mm_HandSolder
U1: MCP2221AxSL; SOIC-14_3.9x8.7mm_P1.27mm

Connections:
unnamed: D1.1 (K), U1.6 (UTx)
unnamed: D1.2 (A), J8.1
unnamed: D2.1 (K), U1.7 (GP2)
unnamed: D2.2 (A), J9.1
unnamed: D3.1 (K), R1.2
unnamed: D4.1 (K), R2.2
unnamed: D5.1 (K), R3.2
unnamed: J1.1, U1.13 (D+)
unnamed: J2.1, U1.12 (D-)
unnamed: D3.2 (A), D4.2 (A), D5.2 (A), J3.1, U1.1 (VDD), U1.11 (VUSB)
unnamed: J4.1, U1.14 (VSS)
unnamed: J5.1, U1.9 (SDA)
unnamed: J6.1, U1.10 (SCL)
unnamed: J7.1, U1.5 (URx)
unnamed: R1.1, U1.2 (GP0)
unnamed: R3.1, U1.3 (GP1)
unnamed: R2.1, U1.8 (GP3)

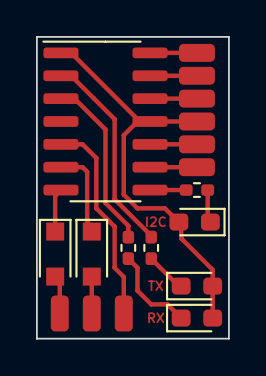
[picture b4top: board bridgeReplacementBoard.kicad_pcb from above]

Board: 2 copper layers, 10.7 x 16.8 mm, 18 parts (0 on the bottom side), 17 nets.

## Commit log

2021-12-15 Added gitignore
2021-12-15 Revision 0.1
2021-12-15 Revision 0.2
2021-12-15 Revision 1.0
2021-12-17 Added CEC pullup
2021-12-17 mend
2021-12-22 Added pull-ups to HPD transistors.
2021-12-28 Changed quartz footprint to allow through hole and smd.
2022-01-04 Silk screen fixes
2022-02-19 New adapter, fix incorrect power assignment of RTD2662 in the schematic
2022-03-12 KiCad version update
2022-04-06 Added MCP2221 patch board
2022-07-04 Finalising
2023-08-23 Added an extra 3.3v filtering cap, fixed label positions in schematic
2023-08-23 Updated schematic and render pictures
2023-12-15 Replace U5, TPS61040DBV with PT4103 (White LED Step-Up Converter).
2023-12-15 Correct LED backlight current equation
2023-12-15 Update schematic picture
2023-12-15 Correct resistor value, replace connector values
2023-12-15 More stuff
2025-05-30 Update KiCAD version
2025-08-13 Use only the positive outputs of PAM8003 (as a unipolar amplifier), because negative outputs can't be tied together.
